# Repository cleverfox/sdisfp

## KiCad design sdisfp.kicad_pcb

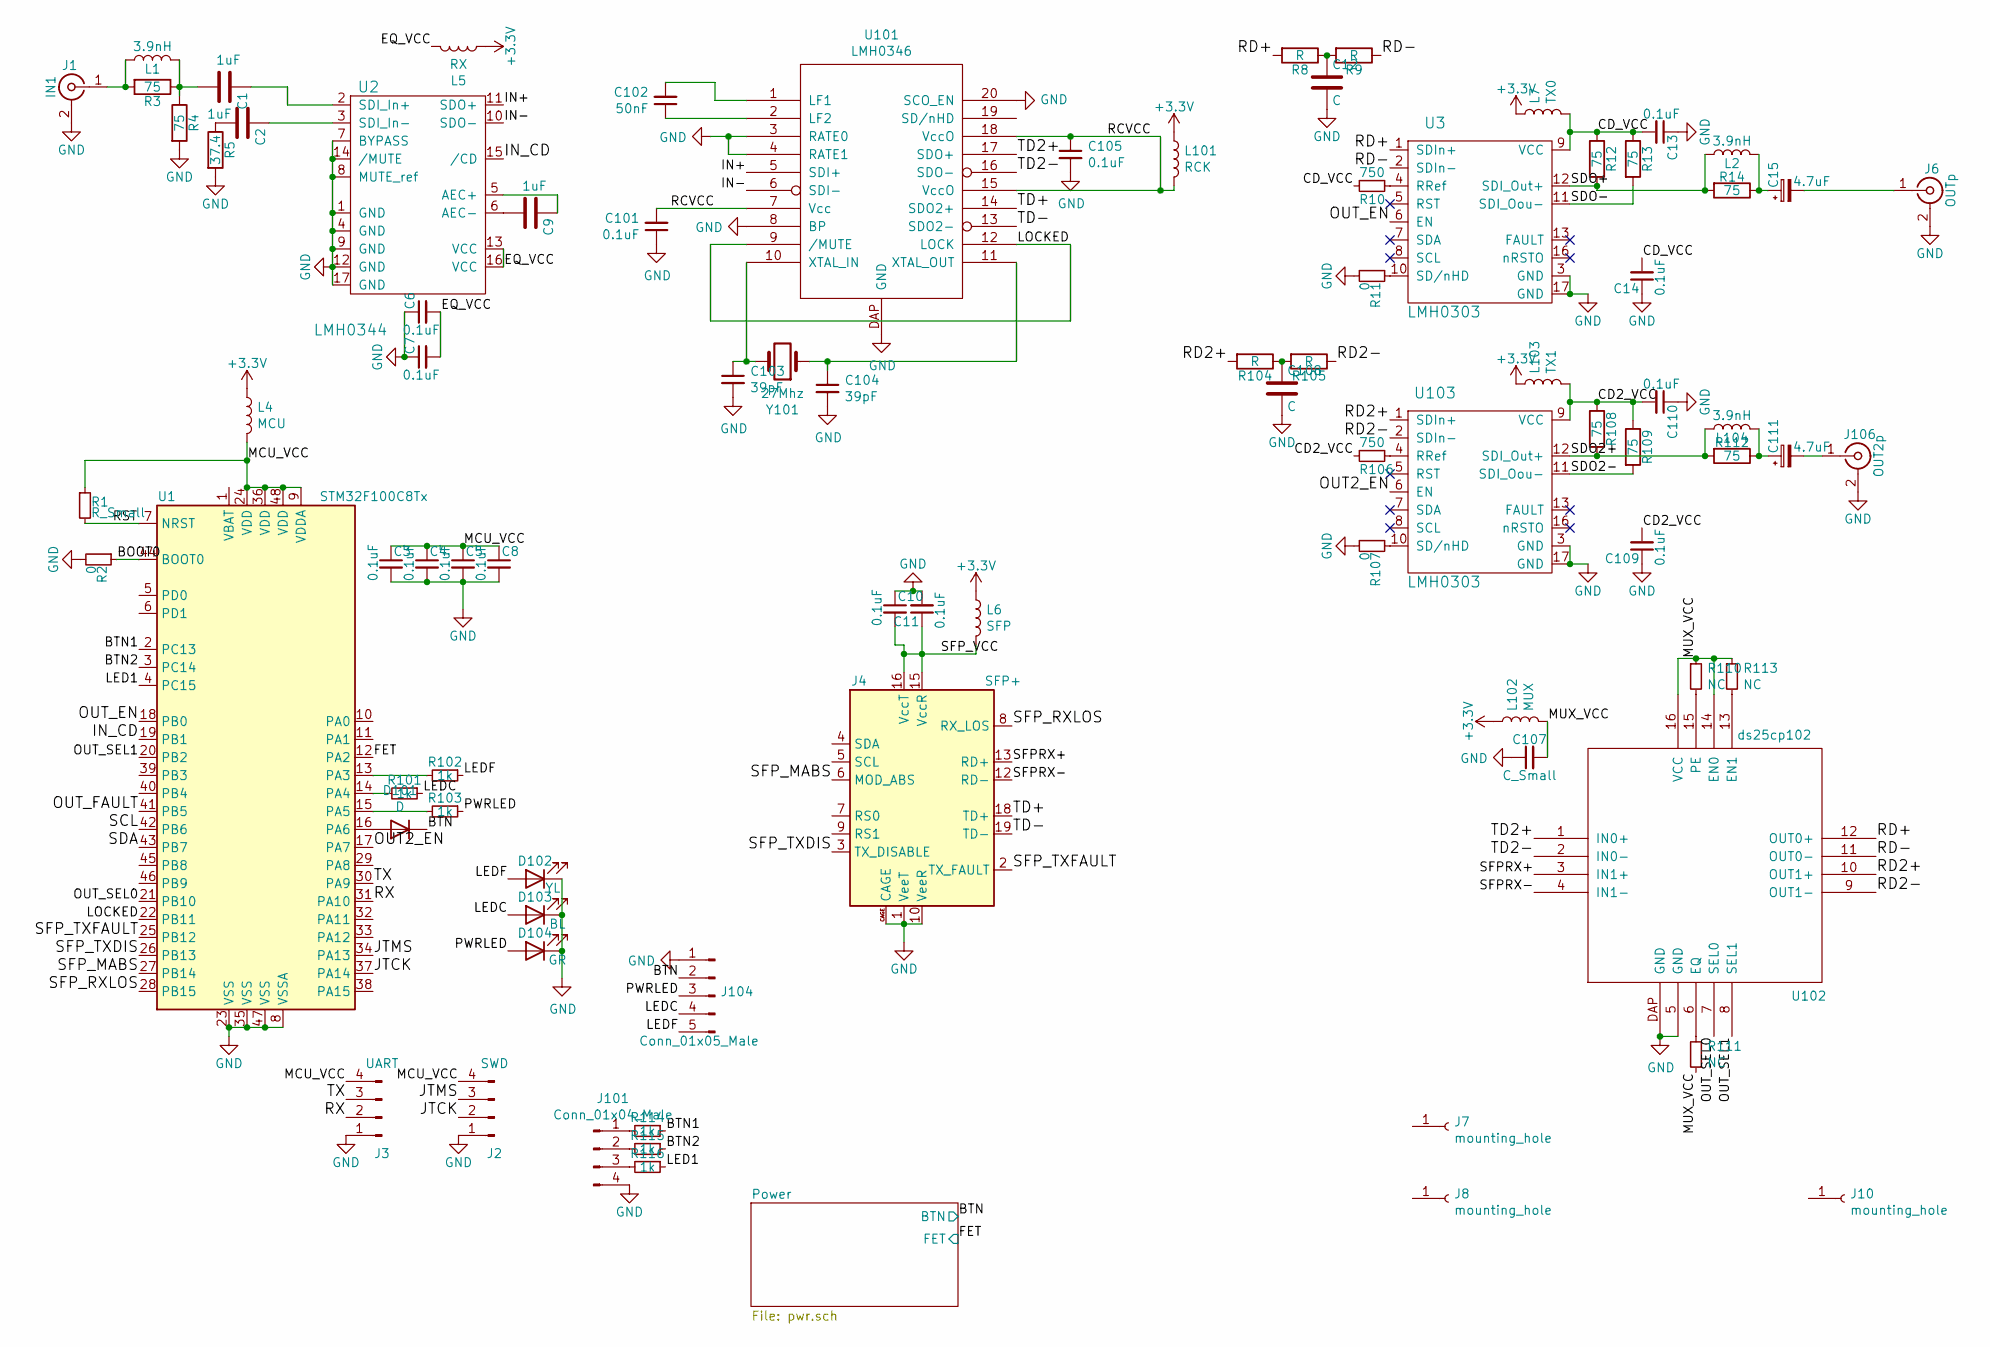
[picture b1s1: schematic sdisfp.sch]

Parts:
C1, C2, C9: 1uF; C_0805_2012Metric
C3, C4, C5, C8: 0.1uF; C_0402_1005Metric
C6, C7, C10, C11, C13, C14, C101, C105, C109, C110: 0.1uF; C_0805_2012Metric
C12, C108: C; C_0805_2012Metric
C15, C111: 4.7uF; C_0805_2012Metric
C102: 50nF; C_0402_1005Metric
C103, C104: 39pF; C_0805_2012Metric
C107: C_Small; C_0402_1005Metric
D101: D; LED_0805_2012Metric
D102: YL; LED_0805_2012Metric
D103: BL; LED_0805_2012Metric
D104: GR; LED_0805_2012Metric
J1: IN1; BNC_Amphenol_B6252HB-NPP3G-50_Horizontal
J2: SWD; PinHeader_1x04_P2.54mm_Vertical
J3: UART; PinHeader_1x04_P2.54mm_Vertical
J4: SFP+; Connector_SFP_and_Cage
J6: OUTp; BNC_Amphenol_B6252HB-NPP3G-50_Horizontal
J7, J8, J10: mounting_hole; MountingHole_3.2mm_M3_DIN965_Pad
J101: Conn_01x04_Male; PinHeader_1x04_P2.54mm_Vertical
J104: Conn_01x05_Male; PinHeader_1x05_P2.54mm_Vertical
J106: OUT2p; BNC_Amphenol_B6252HB-NPP3G-50_Horizontal
L1, L2: 3.9nH; R_0603_1608Metric
L4: MCU; jumper
L5: RX; jumper
L6: SFP; jumper
L7: TX0; jumper
L101: RCK; jumper
L102: MUX; jumper
L103: TX1; jumper
L104: 3.9nH; R_0805_2012Metric
R1: R_Small; R_0402_1005Metric
R2, R11, R107: 0; R_0402_1005Metric
R3, R4, R12, R13, R14, R108, R109, R112: 75; R_0402_1005Metric
R5: 37.4; R_0402_1005Metric
R8, R9, R104, R105: R; R_0402_1005Metric
R10, R106: 750; R_0402_1005Metric
R101, R102, R103, R114, R115, R116: 1k; R_0402_1005Metric
R110, R111, R113: NC; R_0402_1005Metric
U1: STM32F100C8Tx; LQFP-48_7x7mm_P0.5mm
U2: LMH0344; QFN-16-1EP_4x4mm_P0.65mm_EP2.1x2.1mm_ThermalVias
U3, U103: LMH0303; QFN-16-1EP_4x4mm_P0.65mm_EP2.1x2.1mm_ThermalVias
U101: LMH0346; HTSSOP-20-1EP_4.4x6.5mm_P0.65mm_EP2.85x4mm
U102: ds25cp102; QFN-16-1EP_4x4mm_P0.65mm_EP2.1x2.1mm_ThermalVias
Y101: 27Mhz; Crystal_SMD_5032-4Pin_5.0x3.2mm

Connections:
+3V3: L4.1, L5.1, L6.1, L7.1, L101.1, L102.1, L103.1; also elsewhere on the board
/BOOT0: R2.1, U1.44 (BOOT0)
/BTN: D101.1 (K), J104.2; also elsewhere on the board
/BTN1: R114.1, U1.2 (PC13)
/BTN2: R115.1, U1.3 (PC14)
/CD2_VCC: C109.2, C110.2, L103.2, R106.2, R108.1, R109.1, U103.9 (VCC)
/CD_VCC: C13.2, C14.2, L7.2, R10.2, R12.1, R13.1, U3.9 (VCC)
/EQ_VCC: C6.2, C7.2, L5.2, U2.13 (VCC), U2.16 (VCC)
/FET: U1.12 (PA2); also elsewhere on the board
/IN+: U2.11 (SDO+), U101.5 (SDI+)
/IN-: U2.10 (SDO-), U101.6 (SDI-)
/IN_CD: U1.19 (PB1), U2.15 (/CD)
/JTCK: J2.2, U1.37 (PA14)
/JTMS: J2.3, U1.34 (PA13)
/LED1: R116.1, U1.4 (PC15)
/LEDC: D103.2 (A), J104.4, R101.1
/LEDF: D102.2 (A), J104.5, R102.1
/LOCKED: U1.22 (PB11), U101.9 (/MUTE), U101.12 (LOCK)
/MCU_VCC: C3.1, C4.1, C5.1, C8.1, J2.4, J3.4, L4.2, R1.1, U1.9 (VDDA), U1.24 (VDD), U1.36 (VDD), U1.48 (VDD)
/MUX_VCC: C107.2, L102.2, R110.1, R111.1, R113.1, U102.14 (EN0), U102.16 (VCC)
/OUT2_EN: U1.17 (PA7), U103.6 (EN)
/OUT_EN: U1.18 (PB0), U3.6 (EN)
/OUT_FAULT: U1.41 (PB5)
/OUT_SEL0: U1.21 (PB10), U102.7 (SEL0)
/OUT_SEL1: U1.20 (PB2), U102.8 (SEL1)
/PWRLED: D104.2 (A), J104.3, R103.1
/RCVCC: C101.2, C105.1, L101.2, U101.7 (Vcc), U101.15 (VccO), U101.18 (VccO)
/RD2+: R104.2, U102.10 (OUT1+), U103.1 (SDIn+)
/RD2-: R105.1, U102.9 (OUT1-), U103.2 (SDIn-)
/RD+: R8.2, U3.1 (SDIn+), U102.12 (OUT0+)
/RD-: R9.1, U3.2 (SDIn-), U102.11 (OUT0-)
/RST: R1.2, U1.7 (NRST)
/RX: J3.2, U1.31 (PA10)
/SCL: U1.42 (PB6)
/SDA: U1.43 (PB7)
/SDO2+: L104.1, R108.2, R112.2, U103.12 (SDI_Out+)
/SDO2-: R109.2, U103.11 (SDI_Oou-)
/SDO+: L2.1, R12.2, R14.2, U3.12 (SDI_Out+)
/SDO-: R13.2, U3.11 (SDI_Oou-)
/SFPRX+: J4.13 (RD+), U102.3 (IN1+)
/SFPRX-: J4.12 (RD-), U102.4 (IN1-)
/SFP_MABS: J4.6 (MOD_ABS), U1.27 (PB14)
/SFP_RXLOS: J4.8 (RX_LOS), U1.28 (PB15)
/SFP_TXDIS: J4.3 (TX_DISABLE), U1.26 (PB13)
/SFP_TXFAULT: J4.2 (TX_FAULT), U1.25 (PB12)
/SFP_VCC: C10.2, C11.1, J4.15 (VccR), J4.16 (VccT), L6.2
/TD2+: U101.17 (SDO+), U102.1 (IN0+)
/TD2-: U101.16 (SDO-), U102.2 (IN0-)
/TD+: J4.18 (TD+), U101.14 (SDO2+)
/TD-: J4.19 (TD-), U101.13 (SDO2-)
/TX: J3.3, U1.30 (PA9)
GND: C3.2, C4.2, C5.2, C6.1, C7.1, C8.2, C10.1, C11.2, C12.2, C13.1, C14.1, C101.1, C103.2, C104.2, C105.2, C107.1, C108.2, C109.1, C110.1, D102.1 (K), D103.1 (K), D104.1 (K), J1.2 (Ext), J2.1, J3.1, J4.1 (VeeT), J4.10 (VeeR), J4.11 (VeeR), J4.14 (VeeR), J4.17 (VeeT), J4.20 (VeeT), J4.CAGE, J6.2 (Ext), J101.4, J104.1, J106.2 (Ext), R2.2, R4.2, R5.2, R11.2, R107.2, U1.8 (VSSA), U1.23 (VSS), U1.35 (VSS), U1.47 (VSS), U2.1 (GND), U2.4 (GND), U2.7 (BYPASS), U2.8 (MUTE_ref), U2.9 (GND), U2.12 (GND), U2.14 (/MUTE), U2.17 (GND), U3.3 (GND), U3.17 (GND), U101.3 (RATE0), U101.4 (RATE1), U101.8 (BP), U101.20 (SCO_EN), U101.DAP (GND), U102.5 (GND), U102.DAP (GND), U103.3 (GND), U103.17 (GND); also elsewhere on the board
unnamed: C1.1, U2.2 (SDI_In+)
unnamed: C1.2, L1.2, R3.1, R4.1
unnamed: C2.1, U2.3 (SDI_In-)
unnamed: C2.2, R5.1
unnamed: C9.1, U2.5 (AEC+)
unnamed: C9.2, U2.6 (AEC-)
unnamed: C12.1, R8.1, R9.2
unnamed: C15.1, L2.2, R14.1
unnamed: C15.2, J6.1 (In)
unnamed: C102.1, U101.2 (LF2)
unnamed: C102.2, U101.1 (LF1)
unnamed: C103.1, U101.10 (XTAL_IN), Y101.2
unnamed: C104.1, U101.11 (XTAL_OUT), Y101.1
unnamed: C108.1, R104.1, R105.2
unnamed: C111.1, L104.2, R112.1
unnamed: C111.2, J106.1 (In)
unnamed: D101.2 (A), U1.16 (PA6)
unnamed: J1.1 (In), L1.1, R3.2
unnamed: J101.1, R114.2
unnamed: J101.2, R115.2
unnamed: J101.3, R116.2
unnamed: R10.1, U3.4 (RRef)
unnamed: R11.1, U3.10 (SD/nHD)
unnamed: R101.2, U1.14 (PA4)
unnamed: R102.2, U1.13 (PA3)
unnamed: R103.2, U1.15 (PA5)
unnamed: R106.1, U103.4 (RRef)
unnamed: R107.1, U103.10 (SD/nHD)
unnamed: R110.2, U102.15 (PE)
unnamed: R111.2, U102.6 (EQ)
unnamed: R113.2, U102.13 (EN1)

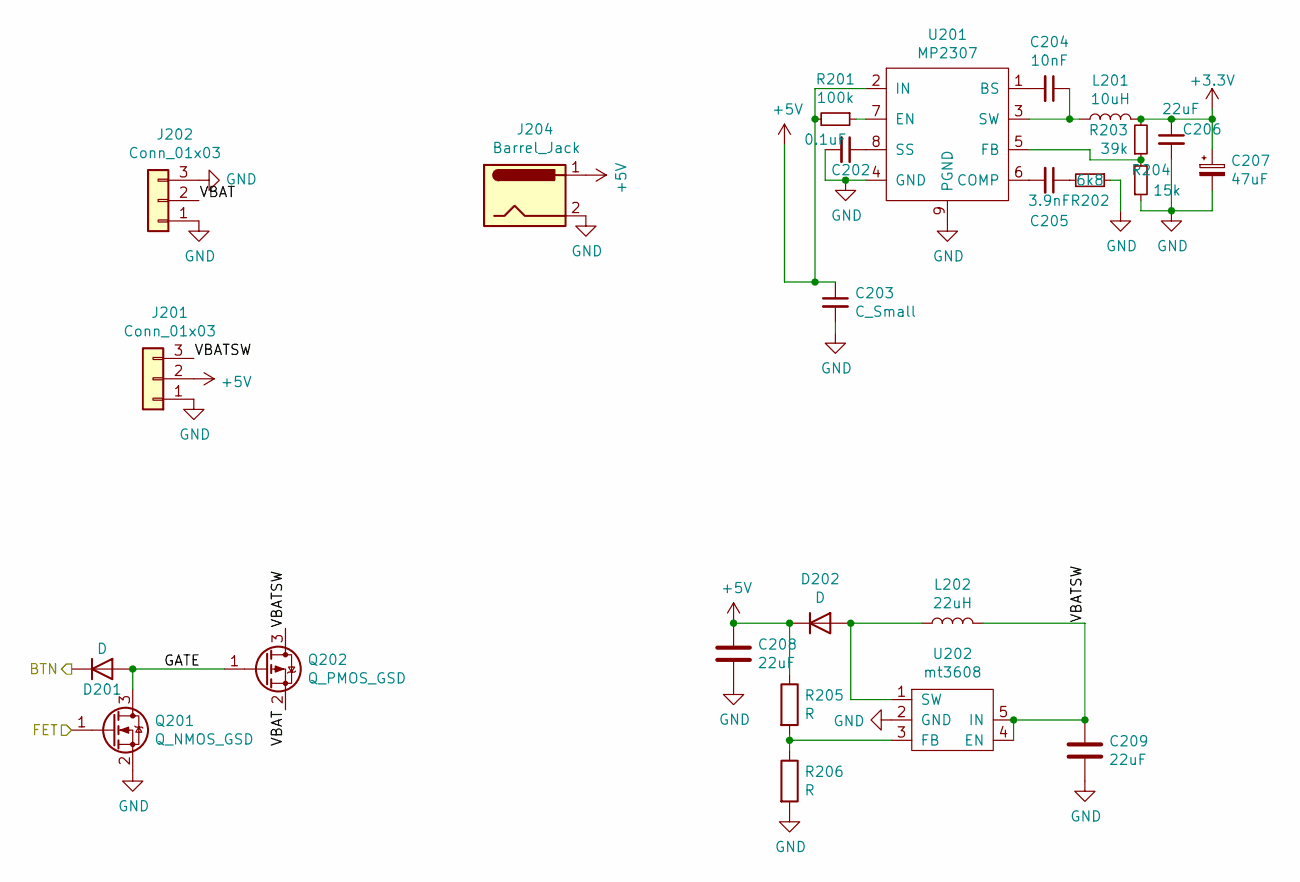
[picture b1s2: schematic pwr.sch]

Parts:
C202: 0.1uF; C_0402_1005Metric
C203: C_Small; C_1206_3216Metric
C204: 10nF; C_0805_2012Metric
C205: 3.9nF; C_0402_1005Metric
C206, C208, C209: 22uF; C_1206_3216Metric
C207: 47uF; CP_EIA-6032-20_AVX-F_Pad2.25x2.35mm_HandSolder
D201: D; LED_0805_2012Metric
D202: D; L_1206_3216Metric
J201, J202: Conn_01x03; PinHeader_1x03_P2.54mm_Vertical
J204: Barrel_Jack; BarrelJack_Horizontal
L201: 10uH; L_7.3x7.3_H3.5
L202: 22uH; L_10.4x10.4_H4.8
Q201: Q_NMOS_GSD; SOT-23
Q202: Q_PMOS_GSD; SOT-23
R201: 100k; R_0402_1005Metric
R202: 6k8; R_0402_1005Metric
R203: 39k; R_0402_1005Metric
R204: 15k; R_0402_1005Metric
R205, R206: R; R_0402_1005Metric
U201: MP2307; SOIC-8-1EP_3.9x4.9mm_P1.27mm_EP2.29x3mm_ThermalVias
U202: mt3608; SOT-23-6

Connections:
+3V3: C206.1, C207.1, L201.2, R203.2; also elsewhere on the board
+5V: C203.1, C208.1, D202.1 (K), J201.2, J204.1, R201.2, R205.1, U201.2 (IN)
/BTN: D201.1 (K); also elsewhere on the board
/FET: Q201.1 (G); also elsewhere on the board
/Power/GATE: D201.2 (A), Q201.3 (D), Q202.1 (G)
/Power/VBAT: J202.2, Q202.2 (S)
/Power/VBATSW: C209.1, J201.3, L202.2, Q202.3 (D), U202.4 (EN), U202.5 (IN)
GND: C202.2, C203.2, C206.2, C207.2, C208.2, C209.2, J201.1, J202.1, J202.3, J204.2, Q201.2 (S), R202.1, R204.1, R206.2, U201.4 (GND), U201.9 (PGND), U202.2 (GND); also elsewhere on the board
unnamed: C202.1, U201.8 (SS)
unnamed: C204.1, L201.1, U201.3 (SW)
unnamed: C204.2, U201.1 (BS)
unnamed: C205.1, R202.2
unnamed: C205.2, U201.6 (COMP)
unnamed: D202.2 (A), L202.1, U202.1 (SW)
unnamed: R201.1, U201.7 (EN)
unnamed: R203.1, R204.2, U201.5 (FB)
unnamed: R205.2, R206.1, U202.3 (FB)

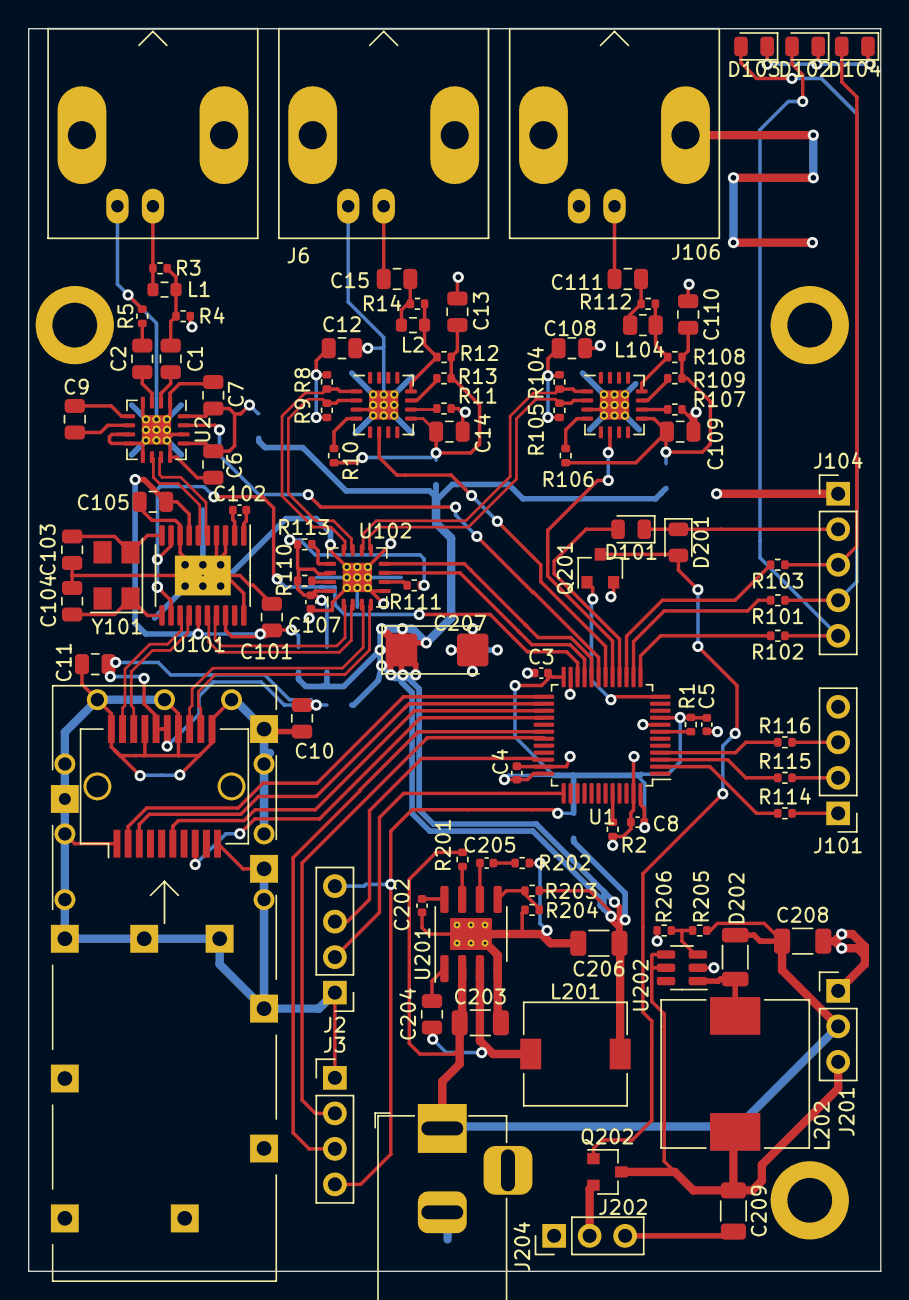
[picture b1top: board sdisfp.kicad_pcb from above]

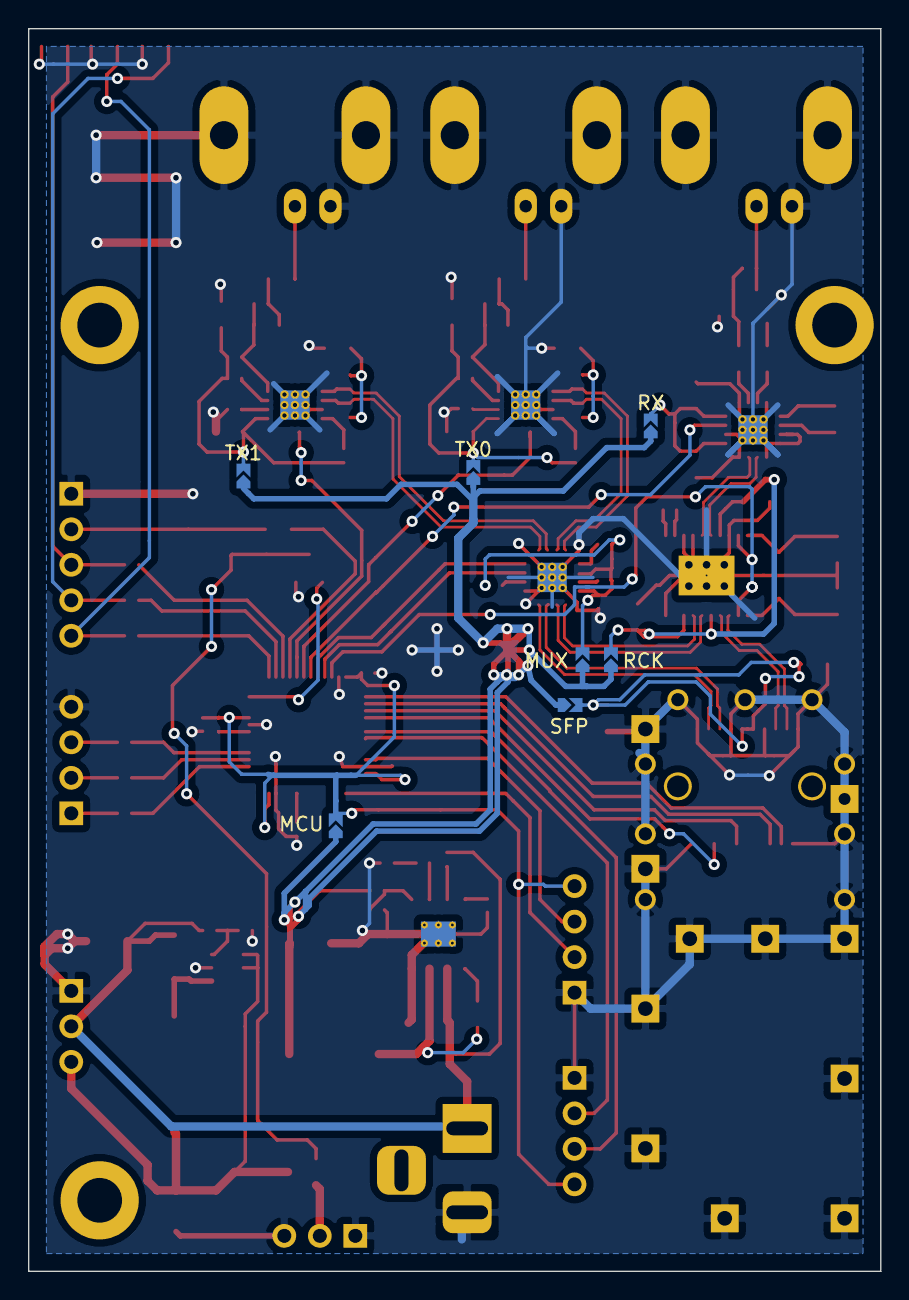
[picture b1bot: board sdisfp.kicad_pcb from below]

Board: 2 copper layers, 61.0 x 88.9 mm, 110 parts (7 on the bottom side), 93 nets.

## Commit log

2021-08-16 schematic in pdf
